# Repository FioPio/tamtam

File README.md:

# tamtam
!!!!!!!!!!!!!!!!!!!!!!!!!!!!!!!UNDER CONSTRUCTION!!!!!!!!!!!!!!!!!!!!!!!!!!!!!!
This repo holds Tamtam (an small low-cost humanoid).
It will contain all the documentation needed to build that litte
robot.
It has 19 DOF, those will be mg90s. I expect to finish it very
son. Since now I have done all of the hardware, the electronics are 
working fine and I've already computed the inverse kinematics.

I am working on the code,and there will be also a document explaining
all the details , since this is my degree project.

the robot is 223.25 mm hight

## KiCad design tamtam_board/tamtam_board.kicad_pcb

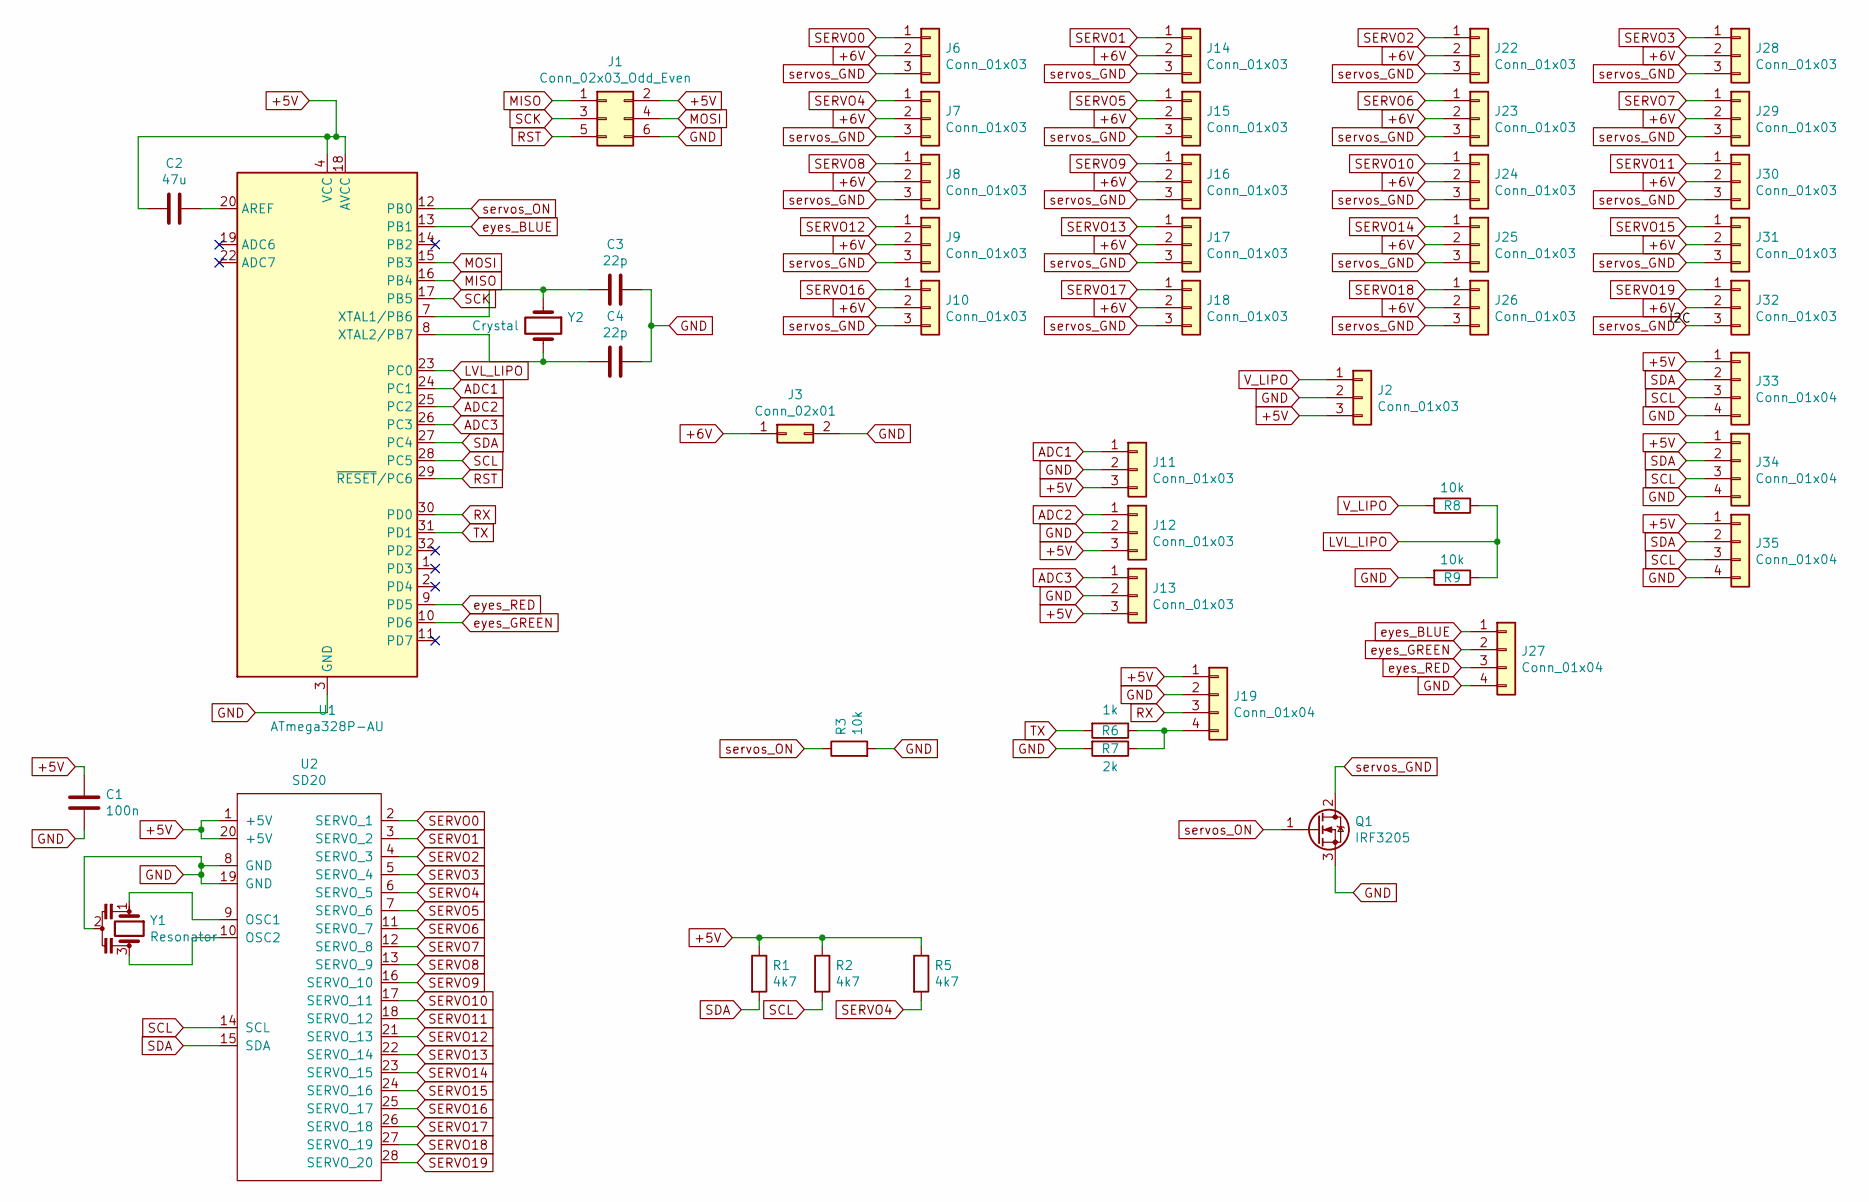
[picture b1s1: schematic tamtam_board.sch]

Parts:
C1: 100n; C_0603_1608Metric_Pad1.05x0.95mm_HandSolder
C2: 47u; C_0603_1608Metric_Pad1.05x0.95mm_HandSolder
C3, C4: 22p; C_0603_1608Metric_Pad1.05x0.95mm_HandSolder
J1: Conn_02x03_Odd_Even; PinHeader_2x03_P2.54mm_Vertical
J2, J6, J7, J8, J9, J10, J11, J12, J13, J14, J15, J16, J17, J18, J22, J23, J24, J25, J26, J28, J29, J30, J31, J32: Conn_01x03; PinHeader_1x03_P2.54mm_Vertical
J3: Conn_02x01; PinHeader_2x01_P2.54mm_Vertical
J19, J27, J33, J34, J35: Conn_01x04; PinHeader_1x04_P2.54mm_Vertical
Q1: IRF3205; TO-220-3_Vertical
R1, R2, R5: 4k7; R_0603_1608Metric_Pad1.05x0.95mm_HandSolder
R3, R8, R9: 10k; R_0603_1608Metric_Pad1.05x0.95mm_HandSolder
R6: 1k; R_0603_1608Metric_Pad1.05x0.95mm_HandSolder
R7: 2k; R_0603_1608Metric_Pad1.05x0.95mm_HandSolder
U1: ATmega328P-AU; TQFP-32_7x7mm_P0.8mm
U2: SD20; DIP-28_W7.62mm_Socket_LongPads
Y1: Resonator; Resonator-3Pin_W7.0mm_H2.5mm
Y2: Crystal; Crystal_HC49-4H_Vertical

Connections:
+5V: C1.1, C2.2, J1.2, J2.3, J11.3, J12.3, J13.3, J19.1, J33.1, J34.1, J35.1, R1.1, R2.1, R5.1, U1.4 (VCC), U1.6 (VCC), U1.18 (AVCC), U2.1 (+5V), U2.20 (+5V)
+6V: J3.1, J6.2, J7.2, J8.2, J9.2, J10.2, J14.2, J15.2, J16.2, J17.2, J18.2, J22.2, J23.2, J24.2, J25.2, J26.2, J28.2, J29.2, J30.2, J31.2, J32.2
ADC1: J11.1, U1.24 (PC1)
ADC2: J12.1, U1.25 (PC2)
ADC3: J13.1, U1.26 (PC3)
GND: C1.2, C3.1, C4.1, J1.6, J2.2, J3.2, J11.2, J12.2, J13.2, J19.2, J27.4, J33.4, J34.4, J35.4, Q1.3 (S), R3.2, R7.2, R9.2, U1.3 (GND), U1.5 (GND), U1.21 (GND), U2.8 (GND), U2.19 (GND), Y1.2
LVL_LIPO: R8.1, R9.1, U1.23 (PC0)
MISO: J1.1, U1.16 (PB4)
MOSI: J1.4, U1.15 (PB3)
unnamed: C2.1, U1.20 (AREF)
unnamed: C3.2, U1.7 (XTAL1/PB6), Y2.1
unnamed: C4.2, U1.8 (XTAL2/PB7), Y2.2
unnamed: J19.4, R6.1, R7.1
unnamed: U2.9 (OSC1), Y1.1
unnamed: U2.10 (OSC2), Y1.3
RST: J1.5, U1.29 (~RESET~/PC6)
RX: J19.3, U1.30 (PD0)
SCK: J1.3, U1.17 (PB5)
SCL: J33.3, J34.3, J35.3, R2.2, U1.28 (PC5), U2.14 (SCL)
SDA: J33.2, J34.2, J35.2, R1.2, U1.27 (PC4), U2.15 (SDA)
SERVO0: J6.1, U2.2 (SERVO_1)
SERVO1: J14.1, U2.3 (SERVO_2)
SERVO2: J22.1, U2.4 (SERVO_3)
SERVO3: J28.1, U2.5 (SERVO_4)
SERVO4: J7.1, R5.2, U2.6 (SERVO_5)
SERVO5: J15.1, U2.7 (SERVO_6)
SERVO6: J23.1, U2.11 (SERVO_7)
SERVO7: J29.1, U2.12 (SERVO_8)
SERVO8: J8.1, U2.13 (SERVO_9)
SERVO9: J16.1, U2.16 (SERVO_10)
SERVO10: J24.1, U2.17 (SERVO_11)
SERVO11: J30.1, U2.18 (SERVO_12)
SERVO12: J9.1, U2.21 (SERVO_13)
SERVO13: J17.1, U2.22 (SERVO_14)
SERVO14: J25.1, U2.23 (SERVO_15)
SERVO15: J31.1, U2.24 (SERVO_16)
SERVO16: J10.1, U2.25 (SERVO_17)
SERVO17: J18.1, U2.26 (SERVO_18)
SERVO18: J26.1, U2.27 (SERVO_19)
SERVO19: J32.1, U2.28 (SERVO_20)
TX: R6.2, U1.31 (PD1)
V_LIPO: J2.1, R8.2
eyes_BLUE: J27.1, U1.13 (PB1)
eyes_GREEN: J27.2, U1.10 (PD6)
eyes_RED: J27.3, U1.9 (PD5)
servos_GND: J6.3, J7.3, J8.3, J9.3, J10.3, J14.3, J15.3, J16.3, J17.3, J18.3, J22.3, J23.3, J24.3, J25.3, J26.3, J28.3, J29.3, J30.3, J31.3, J32.3, Q1.2 (D)
servos_ON: Q1.1 (G), R3.1, U1.12 (PB0)

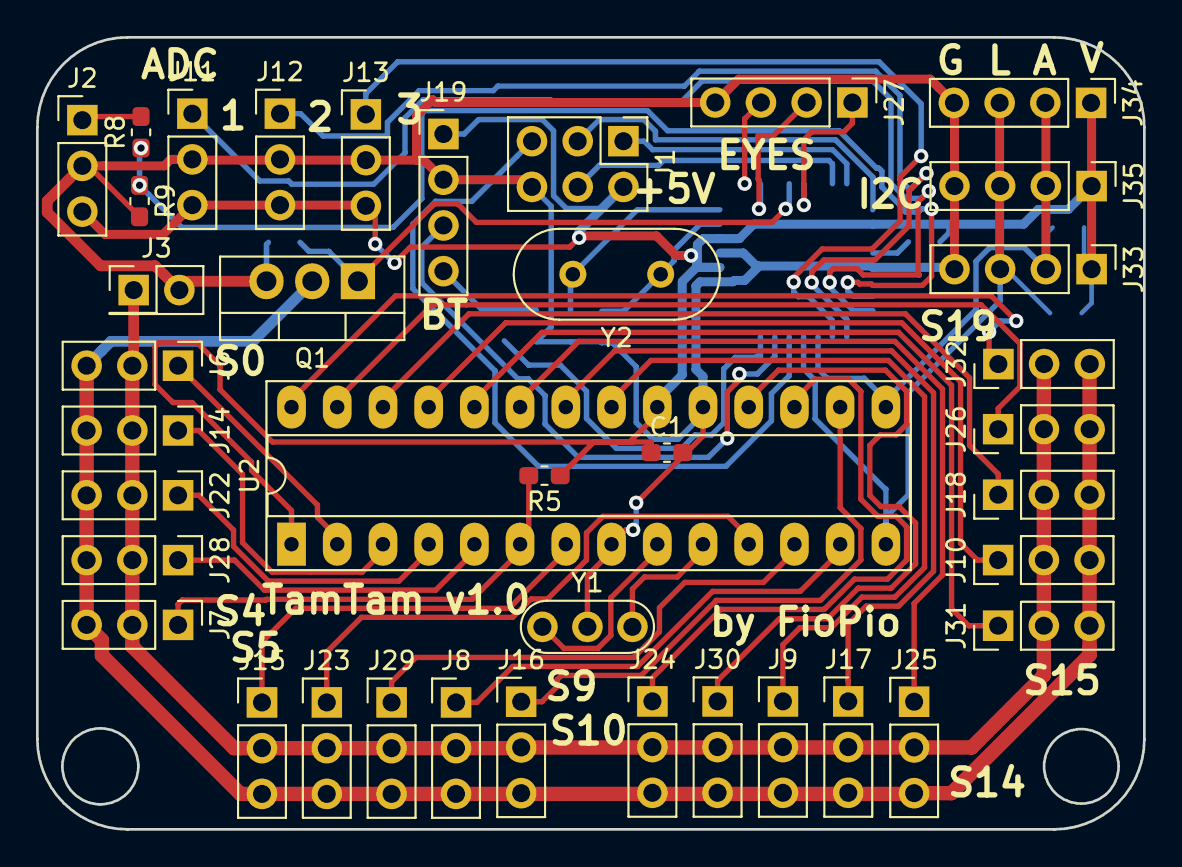
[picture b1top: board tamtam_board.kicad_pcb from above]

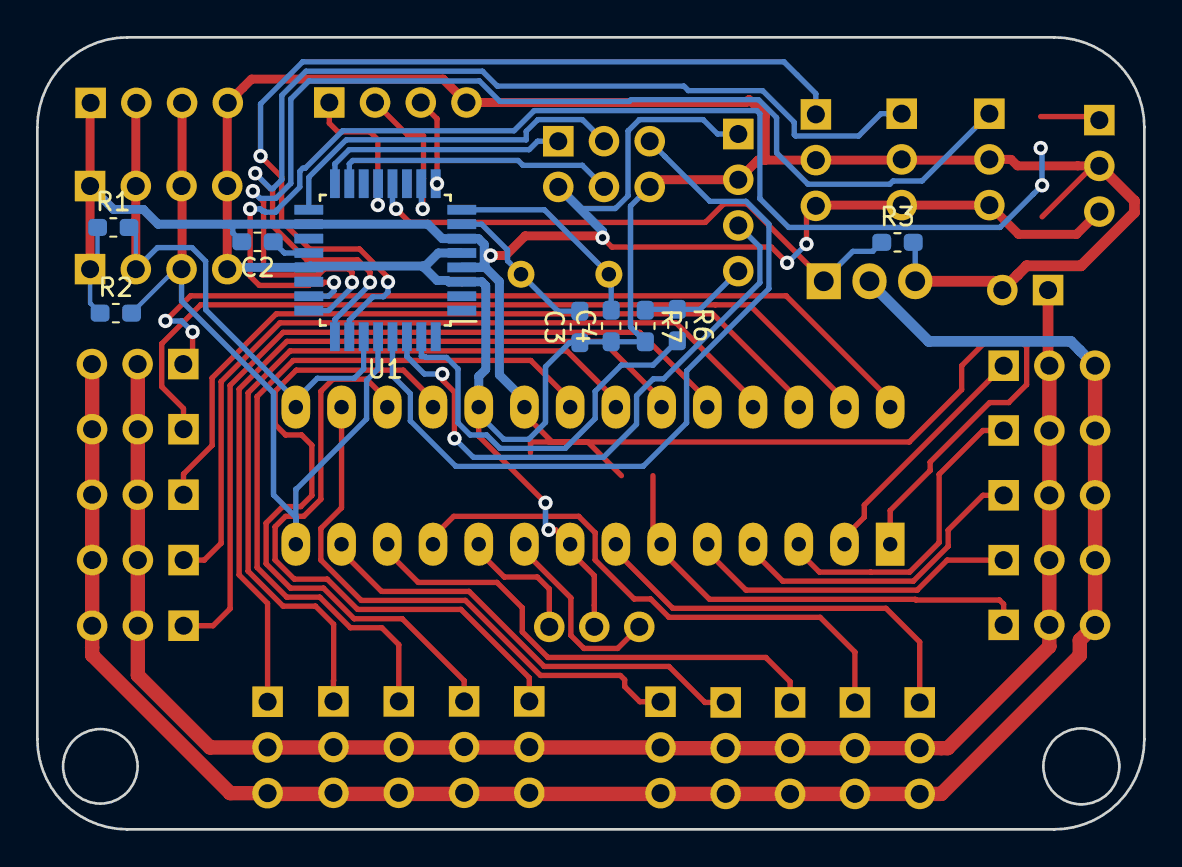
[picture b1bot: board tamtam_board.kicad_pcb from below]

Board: 2 copper layers, 61.5 x 44.0 mm, 48 parts (9 on the bottom side), 47 nets.

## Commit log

2018-12-03 created the mg90s servo model
2018-12-03 README actualization
2018-12-04 Added the first piece, two_servo_holder, and the STL. Small modifies added to the mg90s and materials files.
2018-12-04 small fixes
2018-12-04 deleted unusefull statement
2018-12-04 fixed hole missing
2018-12-04 added axis continuation
2018-12-04 added right foot
2018-12-05 added the lower part of the leg
2018-12-05 updated pieces
2018-12-05 first servo aproximation
2018-12-05 added upper part of the right leg
2018-12-05 new size for the foot
2018-12-06 added description
2018-12-06 added right leg bracket
2018-12-06 updated the right leg bracket
2018-12-06 some updates
2018-12-07 added the new version of body servos holder
2018-12-07 format fixing
2018-12-07 added the board files but not finished
2018-12-07 added some pieces
2018-12-07 updated the body covers
2018-12-07 little more done
2018-12-09 some more work done
2018-12-09 piece updated
2018-12-09 schematic finished
2018-12-09 first board placement design
2018-12-11 board finished
2018-12-11 last changes
2018-12-11 new update
2018-12-11 some component updates
2018-12-14 new head started
2018-12-14 head V2
2018-12-14 finished arms and head
2018-12-14 just a test
2018-12-21 Some last steps before asembling
2019-01-19 A little size difference between the model servo and the real servo makes me to redesign some parts
2019-01-19 a simple code in Arduino and a library to do it easy to program
2019-01-19 Status updated
2019-01-19 added an exlanation about how the invere kinematics have been computed
2019-01-19 inverse kinematics
2019-01-20 some head sizes fixed
2019-01-20 fixed the foot
2019-01-20 some format changed
2019-01-20 little configuration
2019-01-20 configuration things
2019-01-20 definitive foot design
2019-01-29 last version
2019-04-14 updated the two_servo_holder
2019-04-17 head last version
2019-04-17 last version two servo holders
2019-04-18 updated lower leg right
2019-04-22 Last version of TamTam
2019-05-15 back cover modifyed to get more room
2019-05-15 New software version, but still under construction
2019-05-15 added a simplifyed simulator with some examples of walking movement
2019-05-24 starting with ros
2019-05-31 pitch stability control implemented and working
2019-06-05 last hardware version, starting deeply software
